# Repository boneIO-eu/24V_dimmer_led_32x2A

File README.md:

# 24V_dimmer_led_32x2A
24V Dimmer LED 32x2A

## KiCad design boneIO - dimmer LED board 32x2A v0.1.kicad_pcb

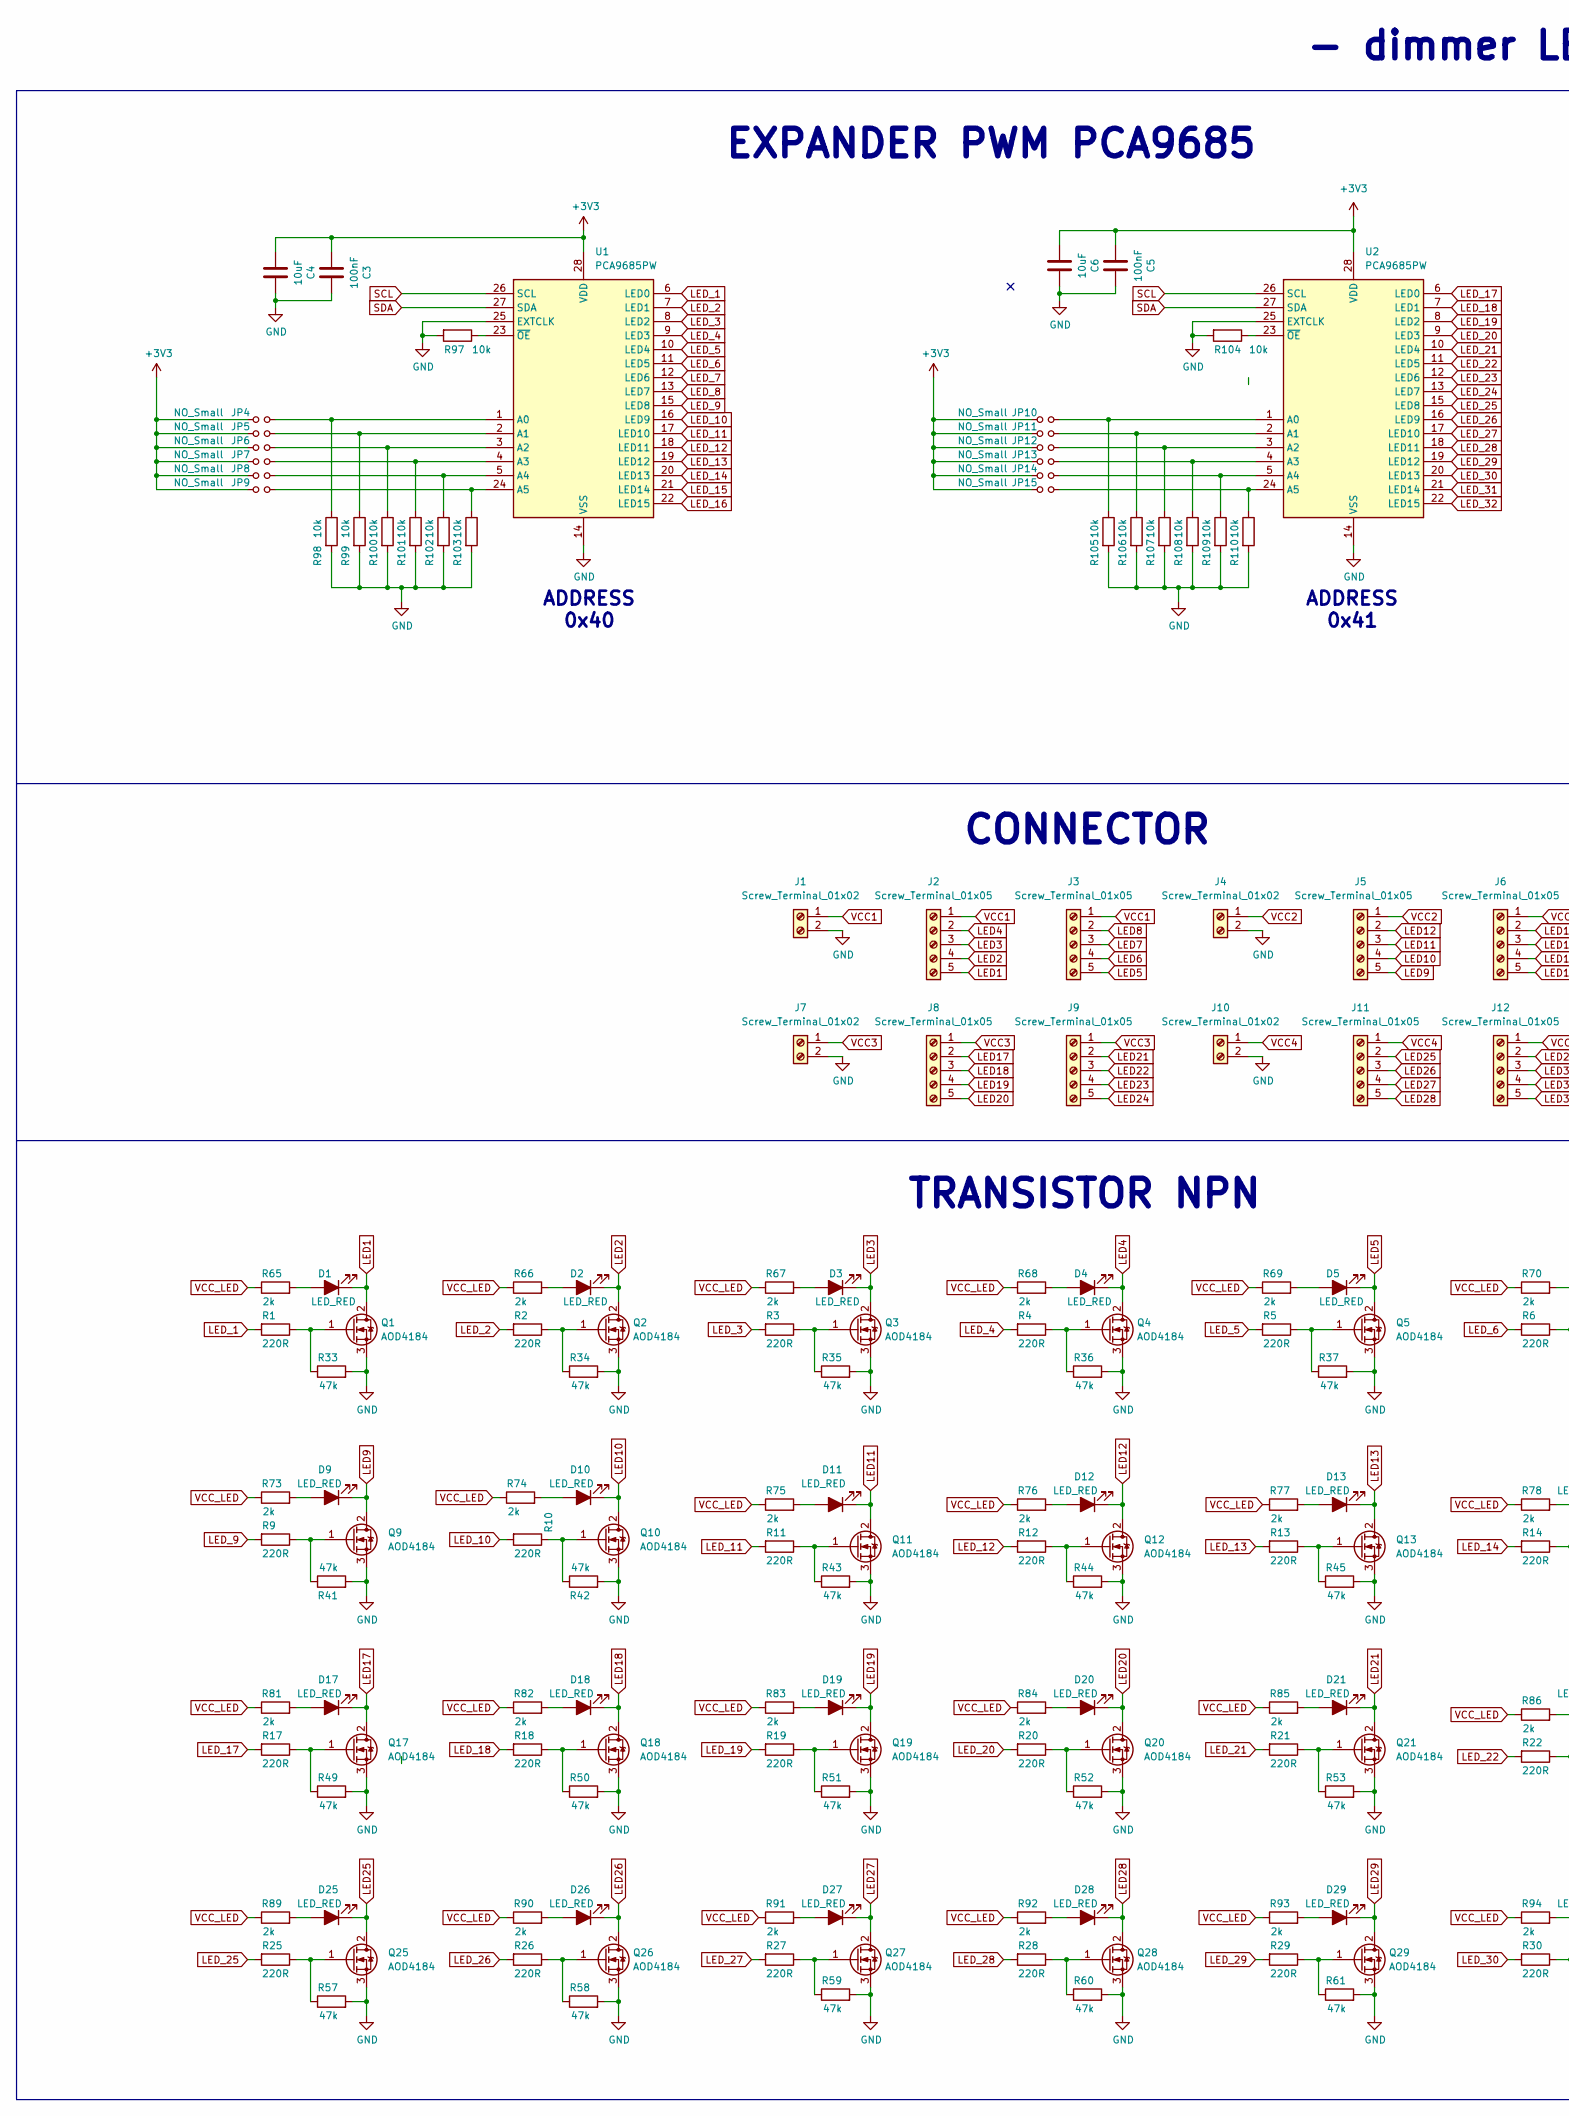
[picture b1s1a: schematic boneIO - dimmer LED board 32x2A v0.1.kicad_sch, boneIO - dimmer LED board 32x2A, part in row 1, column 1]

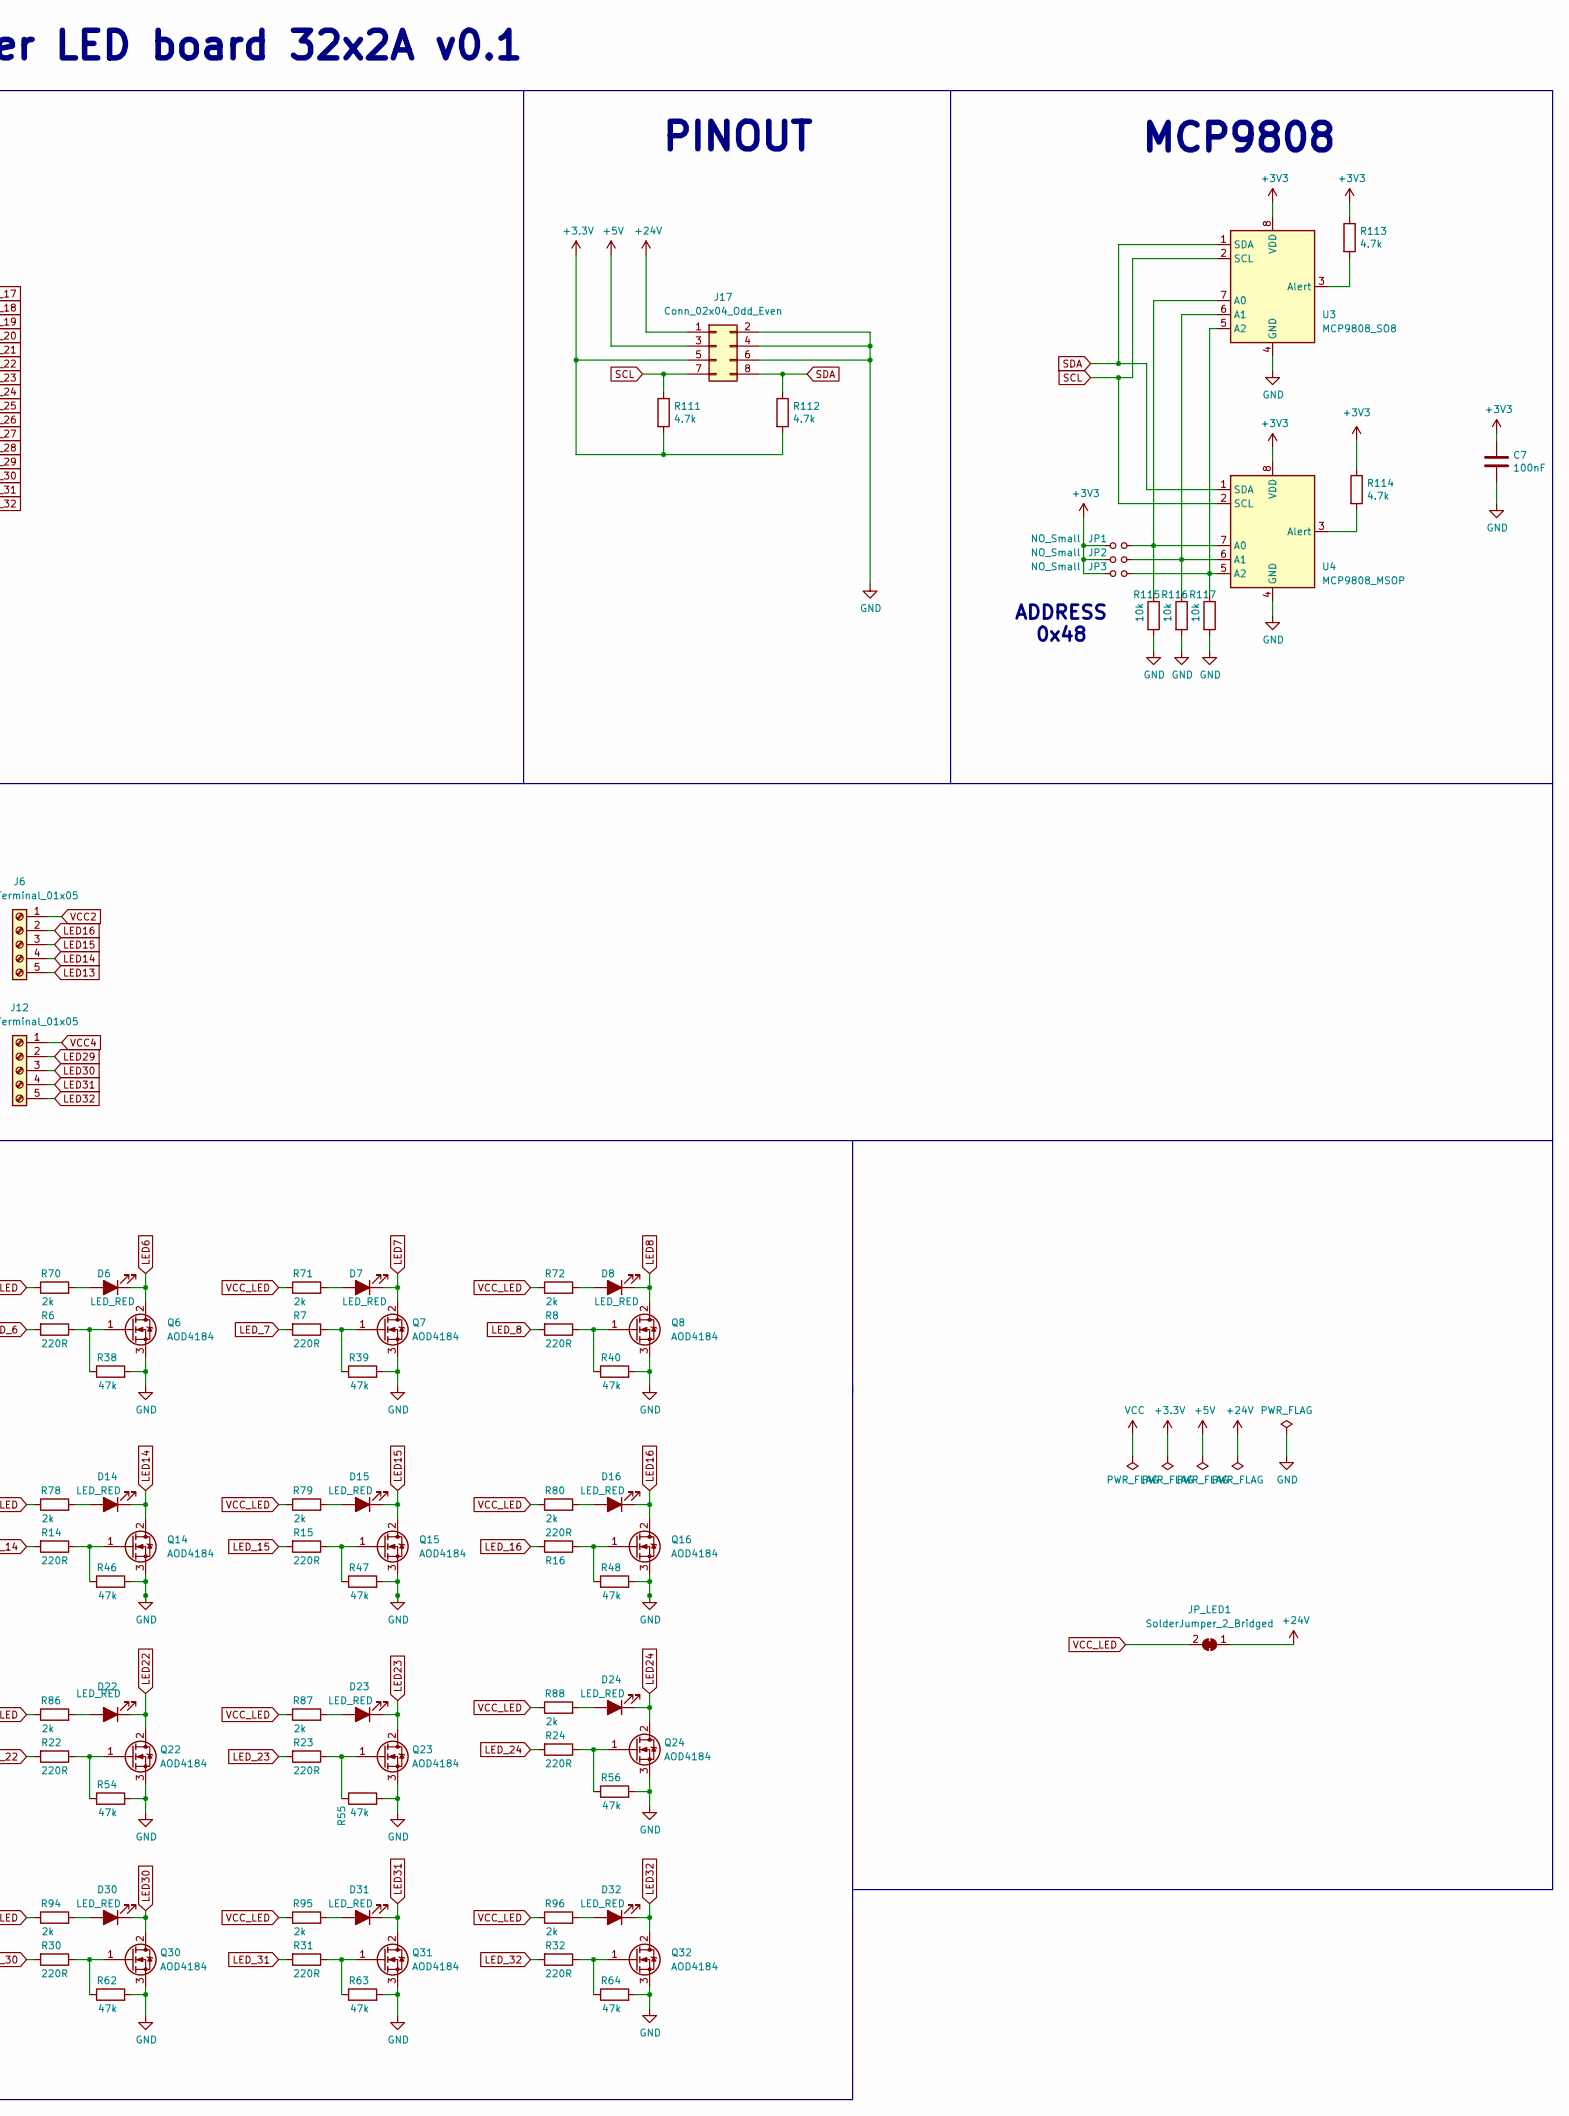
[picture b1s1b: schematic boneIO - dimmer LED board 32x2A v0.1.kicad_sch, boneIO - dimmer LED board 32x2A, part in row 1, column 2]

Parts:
C3, C5, C7: 100nF; C_0603_1608Metric
C4, C6: 10uF; C_0603_1608Metric
D1, D2, D3, D4, D5, D6, D7, D8, D9, D10, D11, D12, D13, D14, D15, D16, D17, D18, D19, D20, D21, D22, D23, D24, D25, D26, D27, D28, D29, D30, D31, D32: LED_RED; LED_0805_2012Metric; JLCPCB C84256
J1, J4, J7, J10: Screw_Terminal_01x02; PhoenixContact_GMSTBA_2,5_2-G_1x02_P7.50mm_Horizontal
J2, J3, J5, J6, J8, J9, J11, J12: Screw_Terminal_01x05; PhoenixContact_GMSTBA_2,5_5-G_1x05_P7.50mm_Horizontal
J17: Conn_02x04_Odd_Even; PinHeader_2x04_P2.54mm_Vertical
JP1, JP2, JP3, JP4, JP5, JP6, JP7, JP8, JP9, JP10, JP11, JP12, JP13, JP14, JP15: NO_Small; SolderJumper-2_P1.3mm_Open_RoundedPad1.0x1.5mm
JP_LED1: SolderJumper_2_Bridged; SolderJumper-2_P1.3mm_Bridged_RoundedPad1.0x1.5mm
Q1, Q2, Q3, Q4, Q5, Q6, Q7, Q8, Q9, Q10, Q11, Q12, Q13, Q14, Q15, Q16, Q17, Q18, Q19, Q20, Q21, Q22, Q23, Q24, Q25, Q26, Q27, Q28, Q29, Q30, Q31, Q32: AOD4184; TO-252-2
R1, R2, R3, R4, R5, R6, R7, R8, R9, R10, R11, R12, R13, R14, R15, R16, R17, R18, R19, R20, R21, R22, R23, R24, R25, R26, R27, R28, R29, R30, R31, R32: 220R; R_0603_1608Metric
R33, R34, R35, R36, R37, R38, R39, R40, R41, R42, R43, R44, R45, R46, R47, R48, R49, R50, R51, R52, R53, R54, R55, R56, R57, R58, R59, R60, R61, R62, R63, R64: 47k; R_0603_1608Metric
R65, R66, R67, R68, R69, R70, R71, R72, R73, R74, R75, R76, R77, R78, R79, R80, R81, R82, R83, R84, R85, R86, R87, R88, R89, R90, R91, R92, R93, R94, R95, R96: 2k; R_0603_1608Metric
R97, R98, R99, R100, R101, R102, R103, R104, R105, R106, R107, R108, R109, R110, R115, R116, R117: 10k; R_0603_1608Metric
R111, R112, R113, R114: 4.7k; R_0603_1608Metric
U1, U2: PCA9685PW; TSSOP-28_4.4x9.7mm_P0.65mm
U3: MCP9808_SO8; SO-8_3.9x4.9mm_P1.27mm
U4: MCP9808_MSOP; MSOP-8_3x3mm_P0.65mm

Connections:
+5V: J17.3
+24V: J17.1, JP_LED1.1 (A)
GND: C3.1, C4.1, C5.1, C6.1, C7.2, J1.2, J4.2, J7.2, J10.2, J17.2, J17.4, J17.6, Q1.3 (S), Q2.3 (S), Q3.3 (S), Q4.3 (S), Q5.3 (S), Q6.3 (S), Q7.3 (S), Q8.3 (S), Q9.3 (S), Q10.3 (S), Q11.3 (S), Q12.3 (S), Q13.3 (S), Q14.3 (S), Q15.3 (S), Q16.3 (S), Q17.3 (S), Q18.3 (S), Q19.3 (S), Q20.3 (S), Q21.3 (S), Q22.3 (S), Q23.3 (S), Q24.3 (S), Q25.3 (S), Q26.3 (S), Q27.3 (S), Q28.3 (S), Q29.3 (S), Q30.3 (S), Q31.3 (S), Q32.3 (S), R33.2, R34.2, R35.2, R36.2, R37.2, R38.2, R39.2, R40.2, R41.2, R42.2, R43.2, R44.2, R45.2, R46.2, R47.2, R48.2, R49.2, R50.2, R51.2, R52.2, R53.2, R54.2, R55.2, R56.2, R57.2, R58.2, R59.2, R60.2, R61.2, R62.2, R63.2, R64.2, R97.2, R98.2, R99.2, R100.2, R101.2, R102.2, R103.2, R104.2, R105.2, R106.2, R107.2, R108.2, R109.2, R110.2, R115.2, R116.2, R117.2, U1.14 (VSS), U1.25 (EXTCLK), U2.14 (VSS), U2.25 (EXTCLK), U3.4 (GND), U4.4 (GND)
LED1: D1.1 (K), J2.5, Q1.2 (D)
LED2: D2.1 (K), J2.4, Q2.2 (D)
LED3: D3.1 (K), J2.3, Q3.2 (D)
LED4: D4.1 (K), J2.2, Q4.2 (D)
LED5: D5.1 (K), J3.5, Q5.2 (D)
LED6: D6.1 (K), J3.4, Q6.2 (D)
LED7: D7.1 (K), J3.3, Q7.2 (D)
LED8: D8.1 (K), J3.2, Q8.2 (D)
LED9: D9.1 (K), J5.5, Q9.2 (D)
LED10: D10.1 (K), J5.4, Q10.2 (D)
LED11: D11.1 (K), J5.3, Q11.2 (D)
LED12: D12.1 (K), J5.2, Q12.2 (D)
LED13: D13.1 (K), J6.5, Q13.2 (D)
LED14: D14.1 (K), J6.4, Q14.2 (D)
LED15: D15.1 (K), J6.3, Q15.2 (D)
LED16: D16.1 (K), J6.2, Q16.2 (D)
LED17: D17.1 (K), J8.2, Q17.2 (D)
LED18: D18.1 (K), J8.3, Q18.2 (D)
LED19: D19.1 (K), J8.4, Q19.2 (D)
LED20: D20.1 (K), J8.5, Q20.2 (D)
LED21: D21.1 (K), J9.2, Q21.2 (D)
LED22: D22.1 (K), J9.3, Q22.2 (D)
LED23: D23.1 (K), J9.4, Q23.2 (D)
LED24: D24.1 (K), J9.5, Q24.2 (D)
LED25: D25.1 (K), J11.2, Q25.2 (D)
LED26: D26.1 (K), J11.3, Q26.2 (D)
LED27: D27.1 (K), J11.4, Q27.2 (D)
LED28: D28.1 (K), J11.5, Q28.2 (D)
LED29: D29.1 (K), J12.2, Q29.2 (D)
LED30: D30.1 (K), J12.3, Q30.2 (D)
LED31: D31.1 (K), J12.4, Q31.2 (D)
LED32: D32.1 (K), J12.5, Q32.2 (D)
LED_1: R1.2, U1.6 (LED0)
LED_2: R2.2, U1.7 (LED1)
LED_3: R3.2, U1.8 (LED2)
LED_4: R4.2, U1.9 (LED3)
LED_5: R5.2, U1.10 (LED4)
LED_6: R6.2, U1.11 (LED5)
LED_7: R7.2, U1.12 (LED6)
LED_8: R8.2, U1.13 (LED7)
LED_9: R9.2, U1.15 (LED8)
LED_10: R10.2, U1.16 (LED9)
LED_11: R11.2, U1.17 (LED10)
LED_12: R12.2, U1.18 (LED11)
LED_13: R13.2, U1.19 (LED12)
LED_14: R14.2, U1.20 (LED13)
LED_15: R15.2, U1.21 (LED14)
LED_16: R16.2, U1.22 (LED15)
LED_17: R17.2, U2.6 (LED0)
LED_18: R18.2, U2.7 (LED1)
LED_19: R19.2, U2.8 (LED2)
LED_20: R20.2, U2.9 (LED3)
LED_21: R21.2, U2.10 (LED4)
LED_22: R22.2, U2.11 (LED5)
LED_23: R23.2, U2.12 (LED6)
LED_24: R24.2, U2.13 (LED7)
LED_25: R25.2, U2.15 (LED8)
LED_26: R26.2, U2.16 (LED9)
LED_27: R27.2, U2.17 (LED10)
LED_28: R28.2, U2.18 (LED11)
LED_29: R29.2, U2.19 (LED12)
LED_30: R30.2, U2.20 (LED13)
LED_31: R31.2, U2.21 (LED14)
LED_32: R32.2, U2.22 (LED15)
unnamed: D1.2 (A), R65.2
unnamed: D2.2 (A), R66.2
unnamed: D3.2 (A), R67.2
unnamed: D4.2 (A), R68.2
unnamed: D5.2 (A), R69.2
unnamed: D6.2 (A), R70.2
unnamed: D7.2 (A), R71.2
unnamed: D8.2 (A), R72.2
unnamed: D9.2 (A), R73.2
unnamed: D10.2 (A), R74.2
unnamed: D11.2 (A), R75.2
unnamed: D12.2 (A), R76.2
unnamed: D13.2 (A), R77.2
unnamed: D14.2 (A), R78.2
unnamed: D15.2 (A), R79.2
unnamed: D16.2 (A), R80.2
unnamed: D17.2 (A), R81.2
unnamed: D18.2 (A), R82.2
unnamed: D19.2 (A), R83.2
unnamed: D20.2 (A), R84.2
unnamed: D21.2 (A), R85.2
unnamed: D22.2 (A), R86.2
unnamed: D23.2 (A), R87.2
unnamed: D24.2 (A), R88.2
unnamed: D25.2 (A), R89.2
unnamed: D26.2 (A), R90.2
unnamed: D27.2 (A), R91.2
unnamed: D28.2 (A), R92.2
unnamed: D29.2 (A), R93.2
unnamed: D30.2 (A), R94.2
unnamed: D31.2 (A), R95.2
unnamed: D32.2 (A), R96.2
unnamed: JP1.2, R115.1, U3.7 (A0), U4.7 (A0)
unnamed: JP2.2, R116.1, U3.6 (A1), U4.6 (A1)
unnamed: JP3.2, R117.1, U3.5 (A2), U4.5 (A2)
unnamed: JP4.2, R98.1, U1.1 (A0)
unnamed: JP5.2, R99.1, U1.2 (A1)
unnamed: JP6.2, R100.1, U1.3 (A2)
unnamed: JP7.2, R101.1, U1.4 (A3)
unnamed: JP8.2, R102.1, U1.5 (A4)
unnamed: JP9.2, R103.1, U1.24 (A5)
unnamed: JP10.2, R105.1, U2.1 (A0)
unnamed: JP11.2, R106.1, U2.2 (A1)
unnamed: JP12.2, R107.1, U2.3 (A2)
unnamed: JP13.2, R108.1, U2.4 (A3)
unnamed: JP14.2, R109.1, U2.5 (A4)
unnamed: JP15.2, R110.1, U2.24 (A5)
unnamed: Q1.1 (G), R1.1, R33.1
unnamed: Q2.1 (G), R2.1, R34.1
unnamed: Q3.1 (G), R3.1, R35.1
unnamed: Q4.1 (G), R4.1, R36.1
unnamed: Q5.1 (G), R5.1, R37.1
unnamed: Q6.1 (G), R6.1, R38.1
unnamed: Q7.1 (G), R7.1, R39.1
unnamed: Q8.1 (G), R8.1, R40.1
unnamed: Q9.1 (G), R9.1, R41.1
unnamed: Q10.1 (G), R10.1, R42.1
unnamed: Q11.1 (G), R11.1, R43.1
unnamed: Q12.1 (G), R12.1, R44.1
unnamed: Q13.1 (G), R13.1, R45.1
unnamed: Q14.1 (G), R14.1, R46.1
unnamed: Q15.1 (G), R15.1, R47.1
unnamed: Q16.1 (G), R16.1, R48.1
unnamed: Q17.1 (G), R17.1, R49.1
unnamed: Q18.1 (G), R18.1, R50.1
unnamed: Q19.1 (G), R19.1, R51.1
unnamed: Q20.1 (G), R20.1, R52.1
unnamed: Q21.1 (G), R21.1, R53.1
unnamed: Q22.1 (G), R22.1, R54.1
unnamed: Q23.1 (G), R23.1, R55.1
unnamed: Q24.1 (G), R24.1, R56.1
unnamed: Q25.1 (G), R25.1, R57.1
unnamed: Q26.1 (G), R26.1, R58.1
unnamed: Q27.1 (G), R27.1, R59.1
unnamed: Q28.1 (G), R28.1, R60.1
unnamed: Q29.1 (G), R29.1, R61.1
unnamed: Q30.1 (G), R30.1, R62.1
unnamed: Q31.1 (G), R31.1, R63.1
unnamed: Q32.1 (G), R32.1, R64.1
unnamed: R97.1, U1.23 (~OE)
unnamed: R104.1, U2.23 (~OE)
unnamed: R113.2, U3.3 (Alert)
unnamed: R114.2, U4.3 (Alert)
SCL: J17.7, R111.1, U1.26 (SCL), U2.26 (SCL), U3.2 (SCL), U4.2 (SCL)
SDA: J17.8, R112.1, U1.27 (SDA), U2.27 (SDA), U3.1 (SDA), U4.1 (SDA)
VCC1: J1.1, J2.1, J3.1
VCC2: J4.1, J5.1, J6.1
VCC3: J7.1, J8.1, J9.1
VCC4: J10.1, J11.1, J12.1
VCC_LED: JP_LED1.2 (B), R65.1, R66.1, R67.1, R68.1, R69.1, R70.1, R71.1, R72.1, R73.1, R74.1, R75.1, R76.1, R77.1, R78.1, R79.1, R80.1, R81.1, R82.1, R83.1, R84.1, R85.1, R86.1, R87.1, R88.1, R89.1, R90.1, R91.1, R92.1, R93.1, R94.1, R95.1, R96.1

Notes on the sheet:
PINOUT
TRANSISTOR NPN
- dimmer LED board 32x2A v0.1
ADDRESS 0x40
ADDRESS 0x41
ADDRESS 0x48
MCP9808
EXPANDER PWM PCA9685
CONNECTOR

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
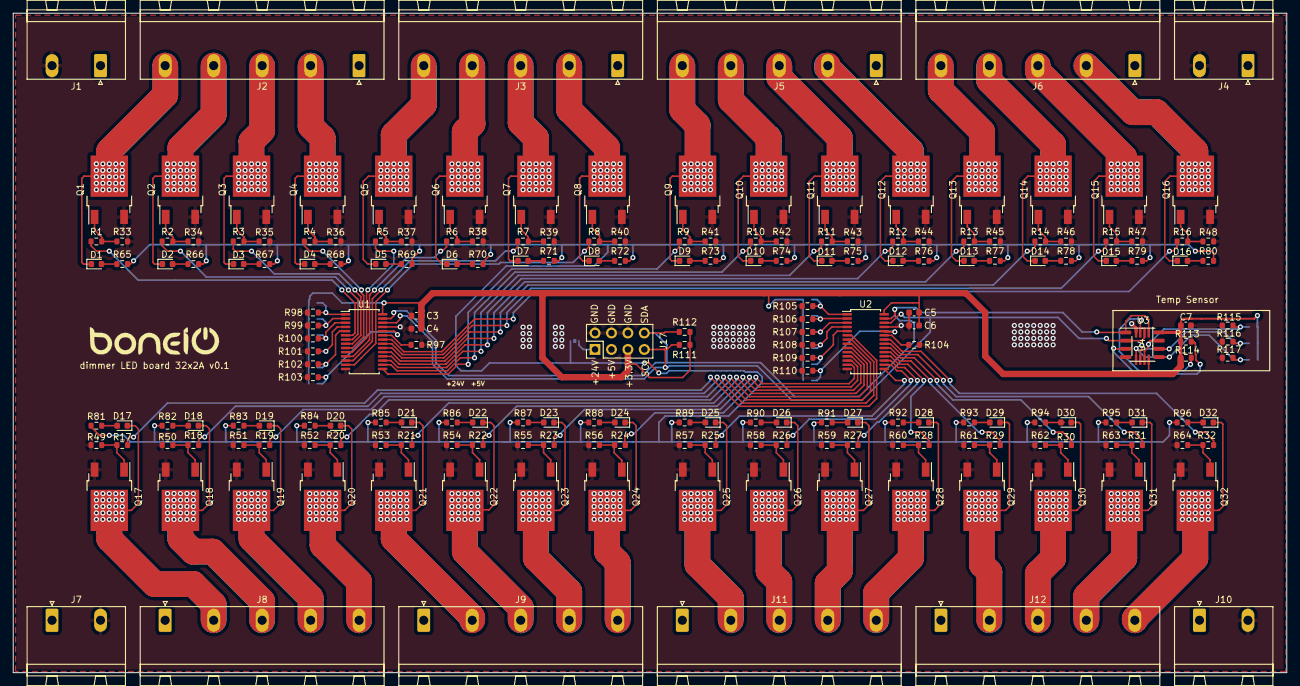
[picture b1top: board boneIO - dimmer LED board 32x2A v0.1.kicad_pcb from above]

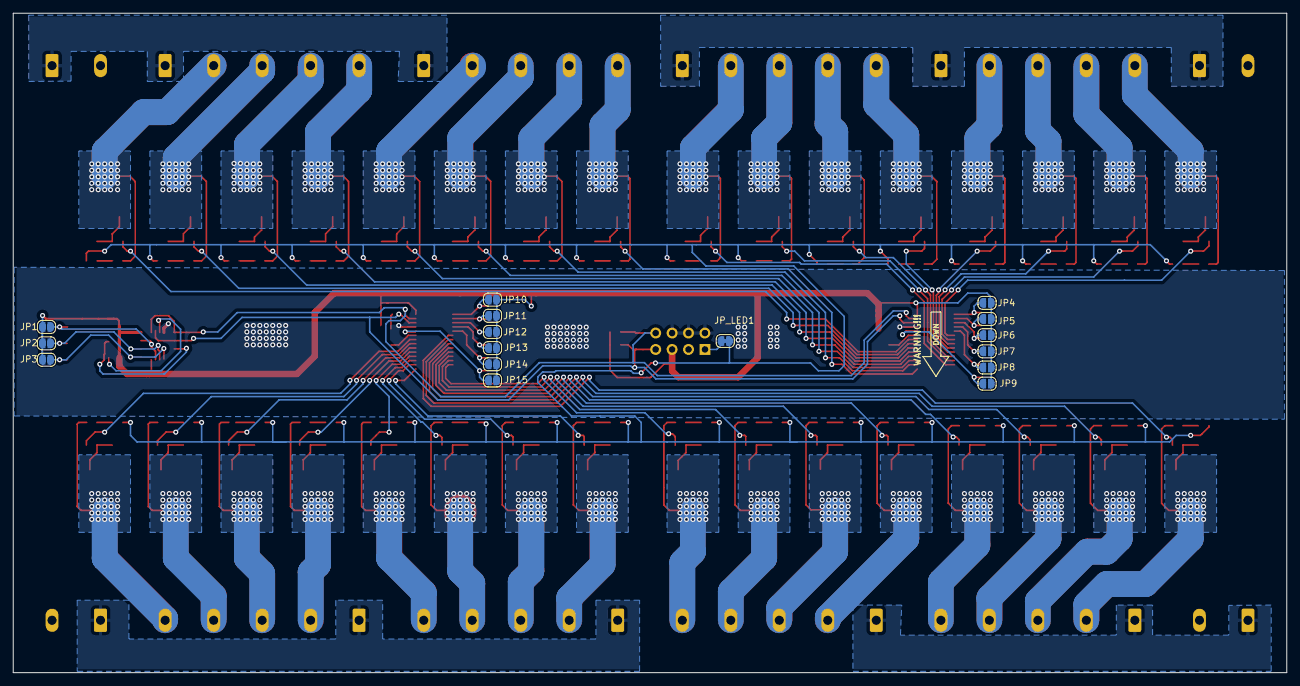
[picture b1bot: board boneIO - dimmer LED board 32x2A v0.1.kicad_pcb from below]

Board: 2 copper layers, 197.0 x 102.0 mm, 219 parts (16 on the bottom side), 157 nets.

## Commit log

2022-03-09 v0.1
